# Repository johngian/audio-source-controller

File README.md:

# DIY audio source controller
## Problem

I have a pair of good audio monitors and want to reuse them between different audio sources.
Extra points if I don't need to move from the couch.

## Solution

Use esp32 and make a network enabled audio source controller.

## Details

* Uses low signal latching relays
* Relays can be driven directly from esp32 using 3.3V gpio ports
* Supports 3 stereo audio inputs and 1 stereo audio output

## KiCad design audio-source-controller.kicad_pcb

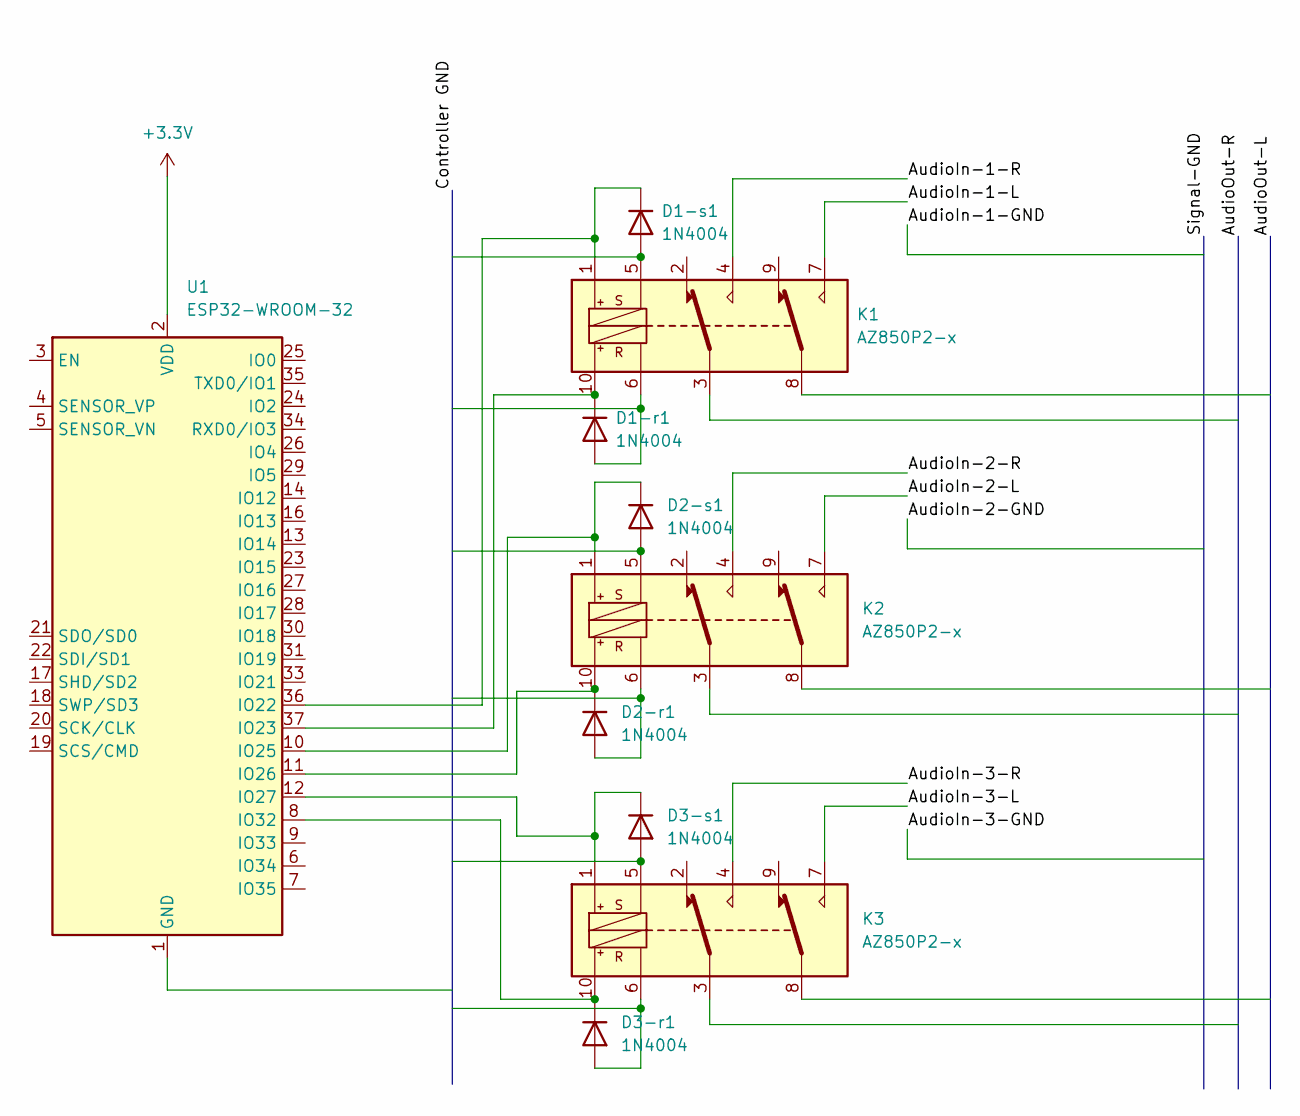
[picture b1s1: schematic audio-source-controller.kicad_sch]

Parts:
D1-r1, D1-s1, D2-r1, D2-s1, D3-r1, D3-s1: 1N4004; D_DO-41_SOD81_P10.16mm_Horizontal
K1, K2, K3: AZ850P2-x; Relay_DPDT_FRT5
U1: ESP32-WROOM-32

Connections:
+3V3: U1.2 (VDD)
/AudioIn-1-L: K1.7
/AudioIn-1-R: K1.4
/AudioIn-2-L: K2.7
/AudioIn-2-R: K2.4
/AudioIn-3-L: K3.7
/AudioIn-3-R: K3.4
unnamed: D1-r1.1 (K), K1.10, U1.37 (IO23)
unnamed: D1-r1.2 (A), K1.6
unnamed: D1-s1.1 (K), K1.1, U1.36 (IO22)
unnamed: D1-s1.2 (A), K1.5
unnamed: D2-r1.1 (K), K2.10, U1.11 (IO26)
unnamed: D2-r1.2 (A), K2.6
unnamed: D2-s1.1 (K), K2.1, U1.10 (IO25)
unnamed: D2-s1.2 (A), K2.5
unnamed: D3-r1.1 (K), K3.10, U1.8 (IO32)
unnamed: D3-r1.2 (A), K3.6
unnamed: D3-s1.1 (K), K3.1, U1.12 (IO27)
unnamed: D3-s1.2 (A), K3.5
unnamed: U1.1 (GND), U1.15 (GND), U1.38 (GND), U1.39 (GND)

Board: 2 copper layers, 10 parts (0 on the bottom side), 13 nets, no tracks yet.

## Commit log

2022-11-06 initial design: Audio source controller
2022-11-06 Ignore local files
2022-11-06 Add basic project information
2022-11-06 Add project license
2022-11-19 Update schematics after ECR
